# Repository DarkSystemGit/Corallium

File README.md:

# Corallium

Corallium is a fantasy console, similar to a previous project of mine, Atto-24. It supports Coral, a C-like language with Rust-inspired syntax, plus built-in graphics, sound, disk, and clock devices.

This repository contains a Coral Compiler, an executable/linking layer, and the VM.

## Quick start

### Requirements

- Rust (Cargo)
- A desktop session (the VM opens a graphics window and initializes audio output)
- X11/XWayland support on Linux, due to the lack of window decorations on Wayland 

### Install
```bash
chmod +x ./install.sh && ./install.sh
```

This script should work for both linux and MacOS, though Mac is untested, along with Windows. Read over the script carefully before running it.
### Run a Coral program
Compile to a cartridge (`.cart`):

```bash
corallium compile --file test/importTest.coral
```

Link one or more extra files or directories into the cartridge:

```bash
corallium compile --file test/importTest.coral --link path/to/file1 path/to/dir
```

Run from a cartridge:

```bash
corallium run --file test/importTest.cart
```
Enable the runtime debugger:

```bash
corallium run --file test/importTest.cart --debug
```

Show CLI help:

```bash
corallium --help
```

### SDK file converters and binary formats

#### MIDI -> `.csfx`

```bash
corallium sdk convert_music path/to/song.mid
```

Optional preview WAV:

```bash
corallium sdk convert_music path/to/song.mid --wav-preview
```

`convert_music` writes `path/to/song.csfx` with this exact layout:

```
CSFX FILE
+------------------------------+
| Header (48 bytes total)      |
| 8 channel records, each:     |
|   pan        : f32 (4 bytes) |
|   event_count: i16 (2 bytes) |
+------------------------------+
| Event Body                   |
| Channel 0 events             |
| Channel 1 events             |
| ...                          |
| Channel 7 events             |
+------------------------------+
```

Each event entry is 10 bytes:

```
+----------------------------+
| timestamp_ms : i32 (4)     |
| frequency_hz : f32 (4)     |
| volume       : i16 (2)     |
+----------------------------+
```

All numeric fields are little-endian.

#### Image -> `.cbmp`

```bash
corallium sdk convert_image path/to/image.png
```

`convert_image` writes `path/to/image.cbmp` with this exact layout:

```
CBMP FILE
+------------------------------+
| width  : i16 (2 bytes)       |
| height : i16 (2 bytes)       |
+------------------------------+
| pixels : width*height*u32    |
|          row-major order     |
+------------------------------+
```

Each pixel is one `u32` value stored little-endian, where the packed color is:

```
0xRRGGBBAA
```

## Coral language

Coral currently includes:

- `let` bindings, arithmetic, bitwise ops, and `as` casts
- `if`/`else`, `while`, `for`, `break`, and `continue`
- `match` expressions with literal, wildcard, enum, union, struct, and optional patterns
- `struct`, `union`, `enum`, and `type` declarations
- optionals (`T?`) with `Some`, `None`, and `try ... catch`
- `defer`, function calls, pointers, arrays, and `sizeof(...)`

Example:

```rust
fn main() -> void {
  let x: i16=1+2+3;
  let y: i16=4*5*6;
  let z: i32=(y as i32)/(x as i32);
  return;
}
```

## Polyp assembly

Polyp is the assembly language for Corallium. See `docs/polyp.md` for the syntax, instruction reference, and examples.

## Specs

- Memory: 16 MiB base RAM, with stack-addressable memory above that range
- Display: 320x240 framebuffer (scaled in a window)
- Audio: 32 kHz output with built-in square/triangle/saw/sample channels
- ISA: integer, float, extended 32-bit, stack, control-flow, call/return, and device I/O ops

Device I/O is invoked as `IO(device_id, command_id)`, with command arguments passed on the VM stack.

## Built-in devices

| Device ID | Device | Command IDs |
| --- | --- | --- |
| `0` | Disk | `0=read`, `1=write`, `2=loadSectors` |
| `1` | Audio | `0=pause`, `1=unpause`, `2=volume`, `3=pan`, `4=frequency`, `5=masterVolume`, `6=loadSound`, `7=setLoop`, `8=schedule`, `9=masterClock` |
| `2` | Clock | `0=read` |
| `3` | Graphics | `0=registerAtlas`, `1=registerLayer`, `2=registerSprite`, `3=render`, `4=pullControls`, `5=setPixel`, `6=getPixel`, `7=removeSprite`, `8=removeLayer`, `9=registerBitmap`, `10=removeBitmap`, `11=deltaTime` |
| `4` | Serial | `0=write (null-terminated string ptr)`, `1=writeNum (i32)` |

Graphics control mapping:

- `A/S/D/F` -> `A/B/X/Y`
- Arrow keys -> D-pad
- `Space` -> Start
- `Q/E` -> Left/Right trigger

## Imports and linking

- `import "module.coral";` loads Coral source modules relative to the importing file
- Importing a `.h` path loads symbols from the header and links a matching precompiled `.bin` library
- `disk::linkedFileStart()` returns the first sector after executable code/data, useful for reading files linked with `--link`

## Project layout

- `src/compiler/` - Coral frontend, AST, IR generation, and backend lowering
- `src/std/` - Coral standard libary
- `src/assembler/` - Polyp frontend, AST, and Code Generation
- `src/executable.rs` - bytecode/function packing, constants, disk image build
- `src/vm.rs` - VM execution engine, stack/memory model, debug console
- `src/devices/` - disk, audio, clock, graphics, and serial drivers
- `test/` - small Coral examples & tests
## Demos

You can run a demo game made for corralium in `demos/strider/strider.cart`. You can run: 
```bash
corallium run --file demos/strider/strider.cart
```

## Credits
Credit to Subspace Audio for the start up sound (sourced from this pack: [512 8-bit sounds](https://opengameart.org/content/512-sound-effects-8-bit-style)).

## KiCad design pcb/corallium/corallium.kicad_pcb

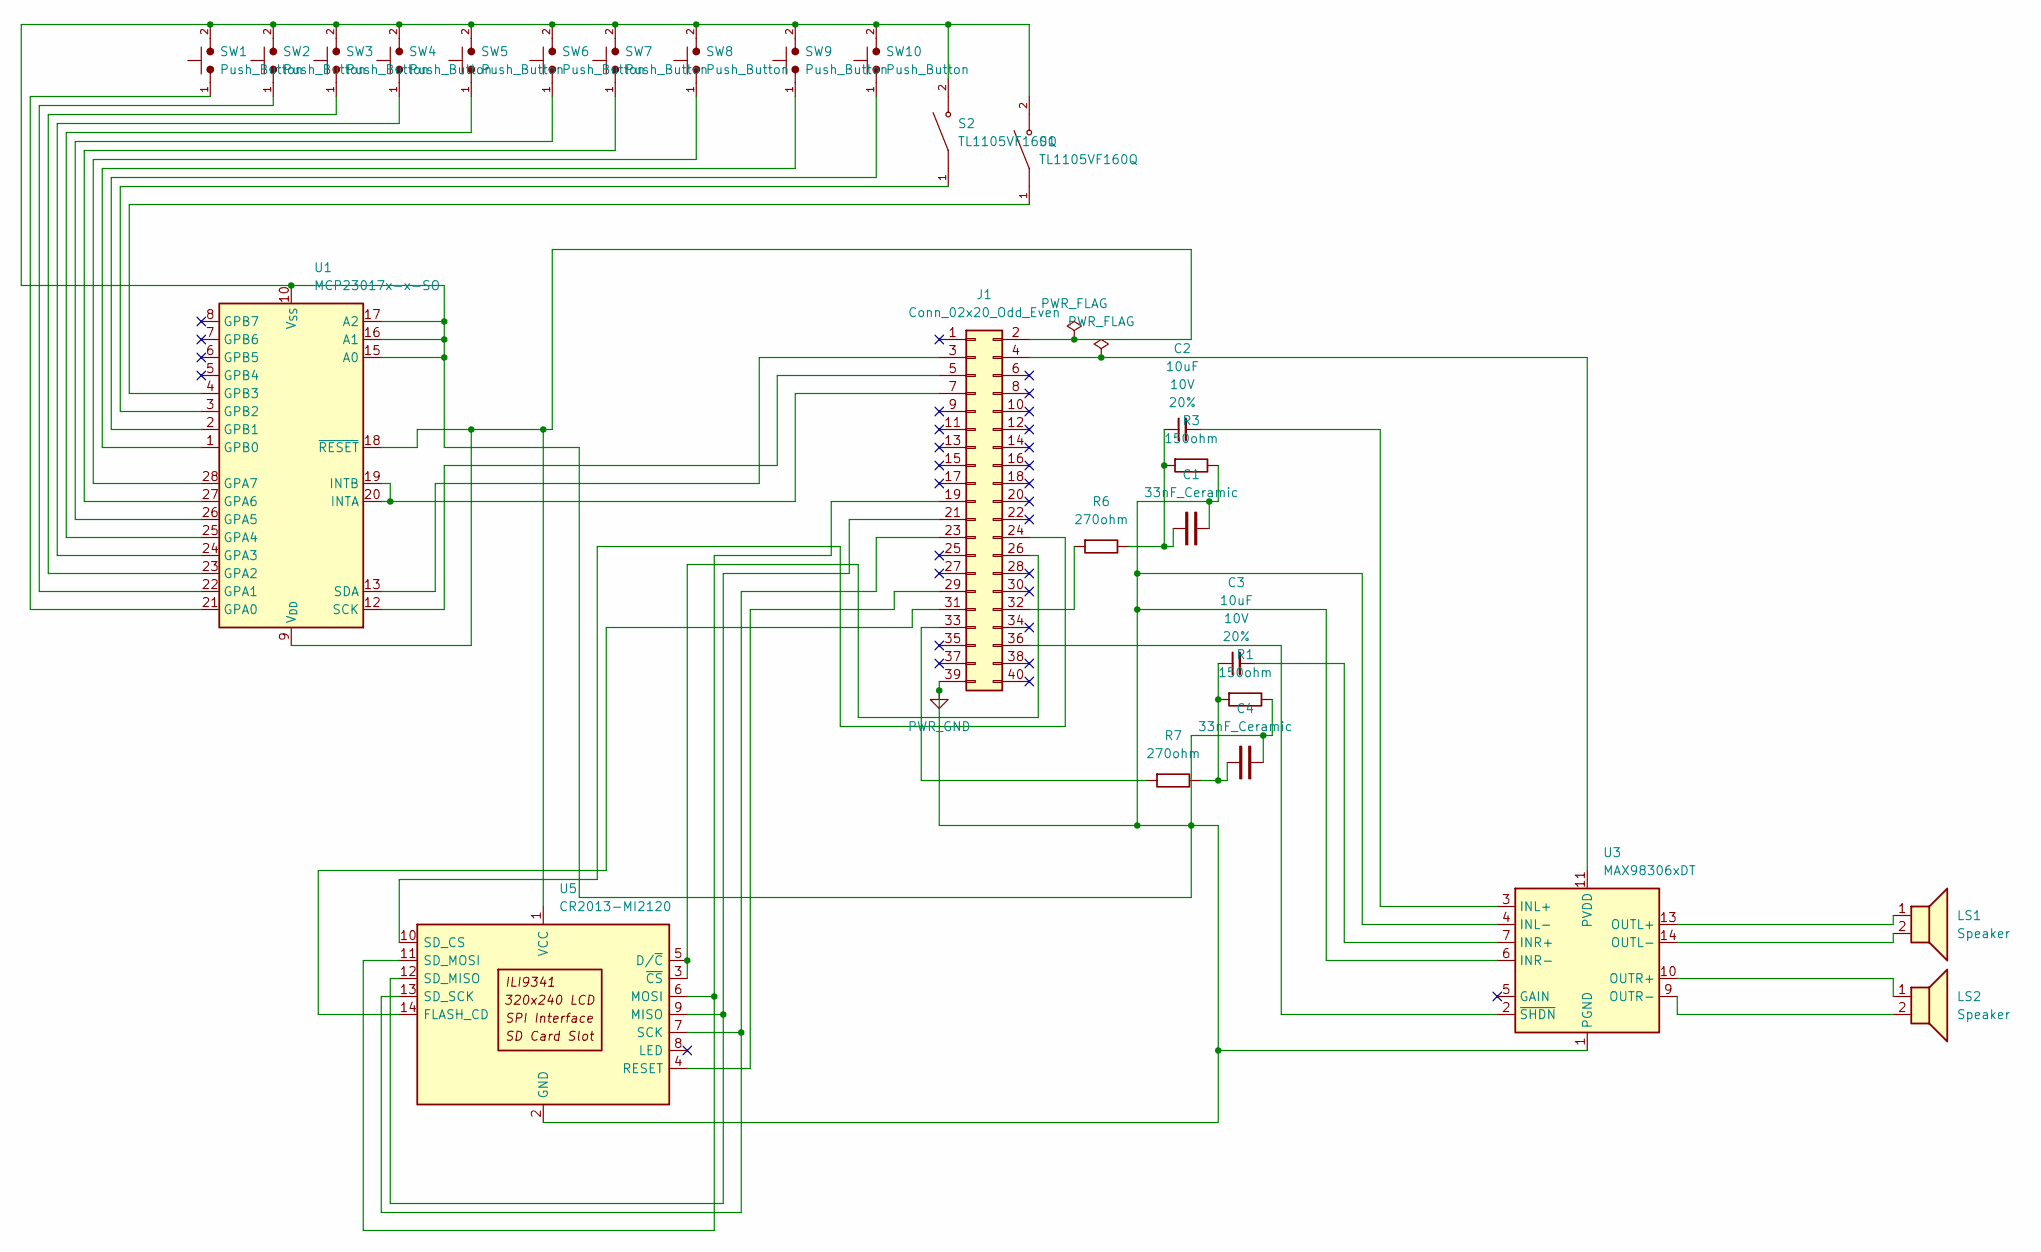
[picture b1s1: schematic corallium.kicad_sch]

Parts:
C1, C4: 33nF_Ceramic; C_Disc_D5.0mm_W2.5mm_P2.50mm
C2, C3: 10uF; C_0603_1608Metric; Voltage 10V; Tolerance 20%
J1: Conn_02x20_Odd_Even; IDC-Header_2x20_P2.54mm_Vertical
LS1, LS2: Speaker; PinHeader_01x02_P2.54mm_Horizontal_SMD
R1, R3: 150ohm; R_Axial_DIN0207_L6.3mm_D2.5mm_P10.16mm_Horizontal
R6, R7: 270ohm; R_Axial_DIN0207_L6.3mm_D2.5mm_P10.16mm_Horizontal
S1, S2: TL1105VF160Q; SW_TL1105VF160Q; PARTREV C
SW1, SW2, SW3, SW4, SW5, SW6, SW7, SW8, SW9, SW10: Push_Button; SW_PUSH_6mm
U1: MCP23017x-x-SO; SOIC-28W_7.5x17.9mm_P1.27mm
U3: MAX98306xDT; TDFN-14-1EP_3x3mm_P0.4mm_EP1.78x2.35mm
U5: CR2013-MI2120

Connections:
unnamed: C1.2, C2.1, R3.1, R6.2
unnamed: C3.1, C4.2, R1.1, R7.2
unnamed: J1.2, U1.9 (V_{DD}), U1.18 (~RESET), U5.1 (VCC)
unnamed: J1.3, U1.13 (SDA)
unnamed: J1.4, U3.11 (PVDD), U3.12 (PVDD)
unnamed: J1.5, U1.12 (SCK)
unnamed: J1.7, U1.19 (INTB), U1.20 (INTA)
unnamed: J1.19, U5.6 (MOSI), U5.11 (SD_MOSI)
unnamed: J1.21, U5.9 (MISO), U5.12 (SD_MISO)
unnamed: J1.23, U5.7 (SCK), U5.13 (SD_SCK)
unnamed: J1.24, U5.10 (SD_CS)
unnamed: J1.26, U5.3 (~CS), U5.5 (D/~C)
unnamed: J1.29, U5.4 (RESET)
unnamed: J1.31, U5.14 (FLASH_CD)
unnamed: J1.32, R6.1
unnamed: J1.33, R7.1
unnamed: J1.36, U3.2 (~SHDN)
unnamed: SW1.1, U1.21 (GPA0)
unnamed: SW2.1, U1.22 (GPA1)
unnamed: SW3.1, U1.23 (GPA2)
unnamed: SW4.1, U1.24 (GPA3)
unnamed: SW5.1, U1.25 (GPA4)
unnamed: SW6.1, U1.26 (GPA5)
unnamed: SW7.1, U1.27 (GPA6)
unnamed: SW8.1, U1.28 (GPA7)
unnamed: SW9.1, U1.1 (GPB0)
unnamed: SW10.1, U1.2 (GPB1)
unnamed 27: S2.1, U1.3 (GPB2); also elsewhere on the board
unnamed 28: S1.1, U1.4 (GPB3); also elsewhere on the board
unnamed: C2.2, U3.3 (INL+)
unnamed: C3.2, U3.7 (INR+)
unnamed: LS1.1, U3.13 (OUTL+)
unnamed: LS1.2, U3.14 (OUTL-)
unnamed: LS2.1, U3.10 (OUTR+)
unnamed: LS2.2, U3.9 (OUTR-)
PWR_GND: C1.1, C4.1, J1.39, R1.2, R3.2, S1.2, S2.2, SW1.2, SW2.2, SW3.2, SW4.2, SW5.2, SW6.2, SW7.2, SW8.2, SW9.2, SW10.2, U1.10 (V_{SS}), U1.15 (A0), U1.16 (A1), U1.17 (A2), U3.1 (PGND), U3.4 (INL-), U3.6 (INR-), U3.8 (PGND), U3.15 (PGND), U5.2 (GND); also elsewhere on the board

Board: 2 copper layers, 26 parts (8 on the bottom side), 36 nets, no tracks yet.

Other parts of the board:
SW11, SW12: Push_Button; SW_PUSH_6mm

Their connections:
unnamed 27: SW11.1; also elsewhere on the board
unnamed 28: SW12.1; also elsewhere on the board
PWR_GND: SW11.2, SW12.2; also elsewhere on the board

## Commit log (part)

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2026-02-04 exprs?
2026-02-18 ir gen finished!
2026-02-22 Register Allocation, Instruction selection & matching. Compiler roughly done
2026-02-24 Unsigned support
2026-02-24 register alloc fixed (default reg supported, ex. r1, ex1, f1)
2026-03-03 backend works! maybe
2026-03-07 defer
2026-03-07 loop test
2026-03-20 Calls and functions working!
2026-03-22 Patching up logic holes, ifs, matches, and more than 2 funcs working!
2026-03-27 IT LIVES!!!!!!!
2026-03-27 optimization(using clanker sry), and making debug easier
2026-03-29 Options implemented, not tested
2026-03-30 Option testing
2026-04-04 implict params begin
2026-04-07 Struct&large data types returning, implicit params, and optionals working!!!!
2026-04-09 Imports!
2026-04-09 some path fixing
2026-04-09 Addl README.md
2026-04-09 small fixes to Cargo.toml
2026-04-10 IT WOKRS (std::gfx for compiler)
2026-04-11 audio, gfx, clock, and serial intergarted!
2026-04-11 disk intergarted!
2026-04-13 STDLIB DONE!!!!!!!!!!!!!!!!!!!!!!!! Coral v1 is done!!!!!!
2026-04-13 docs
2026-04-13 clarity fixes
2026-04-16 fs works
2026-04-19 Demo start, stdlib addtions (fs, conv), gfx fixes
2026-04-19 Revise math notation for affine modes in coral.md
    Updated the math section for affine modes to use LaTeX formatting for better clarity and presentation.
2026-04-27 demo v1!
2026-04-28 Demo pretty much done!
2026-04-28 readme updates
2026-04-29 ALPHA V1!!! WOOOOOOOOOOOOOOOOOOOO
2026-04-29 added demo
2026-04-29 small fix
2026-04-29 installer fixes
2026-06-25 audio engine changes, csfx&cbitmap file formats, polyp assemblhy langauge, graphics engine changes, pcb start
